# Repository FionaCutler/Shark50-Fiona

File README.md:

# Shark50-Fiona
This is following along with [Gondolindrim](https://github.com/Gondolindrim) and Mr. Keebs' stream on PCB design at https://www.twitch.tv/misterkeebs/. Their code is at https://github.com/misterkeebs/Shark50 .

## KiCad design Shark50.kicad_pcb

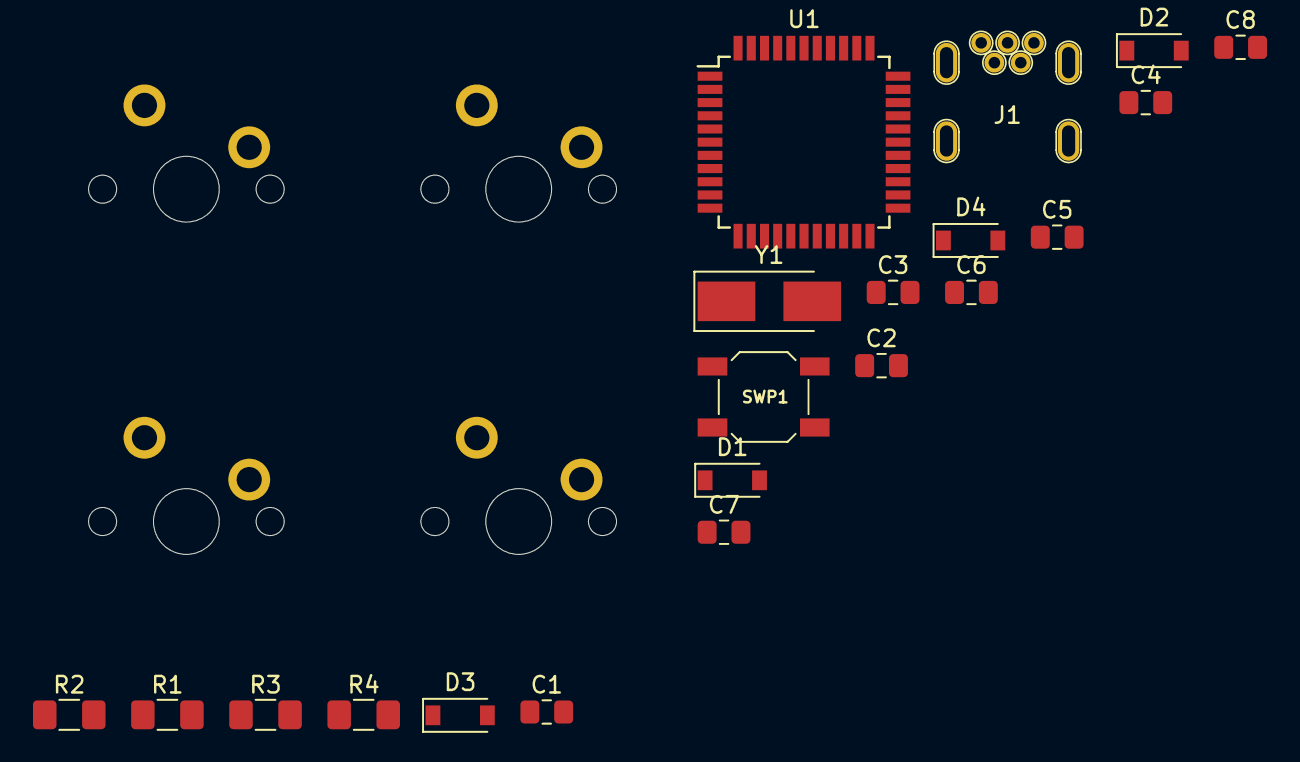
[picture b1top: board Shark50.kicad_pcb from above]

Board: 2 copper layers, 24 parts (0 on the bottom side), 19 nets, no tracks yet.

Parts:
C1, C6: 1u; C_0805_2012Metric_Pad1.15x1.40mm_HandSolder
C2, C3: 22pF; C_0805_2012Metric_Pad1.15x1.40mm_HandSolder
C4: 100nF; C_0805_2012Metric_Pad1.15x1.40mm_HandSolder
C5: 10u; C_0805_2012Metric_Pad1.15x1.40mm_HandSolder
C7, C8: 100n; C_0805_2012Metric_Pad1.15x1.40mm_HandSolder
D1, D2, D3, D4: D_Small; D_SOD-123
J1: USB_B_Mini; USB_MiniB_XM7D-0512
R1, R2: 22R; R_1206_3216Metric_Pad1.42x1.75mm_HandSolder
R3, R4: 10k; R_1206_3216Metric_Pad1.42x1.75mm_HandSolder
SW1, SW2, SW3, SW4: MXSwitch; MX100
SWP1: SW_Push; smdPushBtn
U1: ATmega32U4-AU; TQFP-44_10x10mm_P0.8mm
Y1: 16Mhz; Crystal_SMD_5032-2Pin_5.0x3.2mm_HandSoldering

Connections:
+5V: C5.1, C6.1, C7.1, C8.1, J1.1, R3.1, U1.2, U1.7, U1.14, U1.24, U1.34, U1.44
Col1: SW1.1, SW3.1
Col2: SW2.1, SW4.1
GND: C1.2, C2.2, C3.2, C4.1, C5.2, C6.2, C7.2, C8.2, J1.5, R4.1, SWP1.1, U1.5, U1.15, U1.23, U1.35, U1.43
unnamed: C1.1, U1.6
unnamed: C2.1, U1.17, Y1.1
unnamed: C3.1, U1.16, Y1.2
unnamed: D1.2, SW1.2
unnamed: D2.2, SW2.2
unnamed: D3.2, SW3.2
unnamed: D4.2, SW4.2
unnamed: J1.2, R2.1
unnamed: J1.3, R1.2
unnamed: R1.1, U1.4
unnamed: R2.2, U1.3
unnamed: R4.2, U1.33
RST: C4.2, R3.2, SWP1.2, U1.13
Row1: D1.1, D2.1
Row2: D3.1, D4.1

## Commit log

2019-09-12 made microcontroller circuit and started matrix
2019-09-12 last row
2019-09-12 matrix done
